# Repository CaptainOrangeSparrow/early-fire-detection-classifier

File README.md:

# Early-fire-detection-classifier

## Description

This repository aims to detect fires at an early stage and classify the type of fire using sensor-fusion techniques and machine learning. The project is from the University of Texas at Austin's engineering senior design group Spring 2026.

## Things that are Good to Know

### GIT

Git on the jetson is setup using the SSH key route. Any git actions will not prompt a log in due to the stored SSH deploy key. Pushes will be recorded as have been made by the deploy key. Whoever is registered on the jetson's git config global user.email will show up as the user responsible of a commit at the time of commit.

To change the git config global user:

```git config --global user.email [git email here]```

When you want to do a COMMIT, change the git config global user email to your git email or sign your first name at the end of your commit message (For example add file -firstname).

Once you attempt to PUSH your changes, you will then be prompted with the following message to provide a passphrase for security (this passphrase is shared among the team members):

```Enter passphrase for key '/home/firedistinguisher/.ssh/id_ed25519':```

AFTER you finish pushing your changes and making edits, consider running the following command to clear the user.email environment variable so the next developer will be automatically reminded to provide their email when making their commits, thanks!

```git config --global --unset user.email```

-----

### SSH

To log onto the jetson from the ECE-LRC servers:

```ssh firedistinguisher@localhost -p 2000```

To log onto the jetson from the ECE-LRC servers with video forwarding:

```ssh firedistinguisher@localhost -p 2000 -Y```

To log onto the jetson from your laptop through the ECE-LRC servers to support web-streaming from local host on the jeston to your local browser:

```ssh ssh -J eid@mario.ece.utexas.edu -p 2000 firedistinguisher@localhost -L [port]:localhost:[port]```

- Replace [port] with the port number the web stream is hosted on or streaming to

-----

### CONDA Virtual Environment Manager

Available CONDA environments:

- base
- app
- appgui
- cameragui
- recording
- telemetry

Please do not modify the base environment.

-----

## Repository Structure

**I2C-testing**

This folder contains code to test accessing read-write functionality on the I2C bus using python smbus2 module for various connected devices including the ADC and HDC. Use i2cdetect -r to scan I2C busses for connected devices.

- ```basic-I2C.py``` sends read and write commands on the i2c bus
- ```ads1115-i2c.py``` is a class that reads values from the ads1115 modules
- ```hdc3022.py``` is a class that reads values from the hdc3022 temp and humidity sensor

Requires ```recording``` conda env.

-----

**audio-testing**

This folder contains code for testing the MAX98357A Audio Amp for producing audio from the jetson using the I2S protocol. 

- ```play-tone.py``` plays a sine wave for a specified duration and frequency
- ```play-wav.py``` plays a wav file

Requires ```recording``` conda env.

-----

**camera-gui**

This folder contains original python gui that was developed to play prerecorded mp4 files. A pyside 6 gui application is used to display the videos and interactive buttons.

- ```camera_gui.ipynb``` is the original python notebook that was used to develop the initial gui
- ```camera_gui.py``` is the python version of the ipynb notebook  
- ```test.txt``` is a test file

Requires ```cameragui``` conda env.

-----

**camera-testing**

This folder contains tools to view the raw camera streams for RGB and IR cameras. In particular, it contains code for the tc001. The raw camera streams open native openCV windows or host a web stream. NOTE: The tc001 code came from another repo leswright pythermalcam and contains some erroneous temperature decoding code. (That is fixed in the data recording camera module)

- ```readme```: This folder comes with its own readme. See readme for more details
- ```web-stream-camera.py``` is the web stream version of stream-camera.py. Note: to use the web-stream, the ssh port forwarding needs to be used. (See web stream ssh command above).

Requires ```cameragui``` conda env.

-----

**data-recording**

This is the main data recording software folder. Multi-modal data is recorded and streamed using either a pyside6 gui application, console only mode, or web stream application (recommended). Data is recorded at a default 25 FPS.

Recordings are saved to saved_recordings [dir] and test_recordings [dir] hold recordings that were taken just for testing and are kept for historical purposes.

- ```readme.txt```: This folder comes with its own readme. See readme for more details
- ```record.py``` is the main data recording script```
- ```utilities``` [dir] holds utility modules such as writers, web stream host server, html, javascript, etc. and other helpful utility code
- ```peripherals``` [dir] holds modules containing classes to read info and interact with connected external devices such as cameras and adcs.
- ```saved_recordings``` [dir] holds saved recordings
- ```test_recordings``` [dir] holds test recordings
- ```clear_Saved_to_test.py``` is a helper script to move all recordings in saved_recordings to test_recordings
- ```gstreamer_test.py``` is a helper script to test using gstreamer to run nvidia hardware optimized camera frames
- ```verify-frame-count.py``` is a helper script to count the number of frames in every mp4 file in a specified directory (does not search child directories)

Requires ```recording``` conda env.

-----

**downloads**

The purpose of this folder is to store files in transit (Files that needed to be copied over into or exported out of the jeston).

-----

**stream-camera-gui**

This folder contains files to stream both RGB and IR camera feeds simultaneously with a more custom gui in a pyside6 application

- ```readme.txt```: This folder comes with its own readme. See readme for more details. This readme has details for the rest of the components in the folder and therefore the other contents in the folder won't be listed again here.

Requires ```appgui``` conda env.

-----

**telemetry-display**

This folder contains files to stream data to a ST7735 LCD display.

Requires ```telemetry``` conda env.

-----

**test-files**

This folder contains miscellaneous test files.

----

## Additional Notes

Thanks, add anything other considerations here if need be.

Michael

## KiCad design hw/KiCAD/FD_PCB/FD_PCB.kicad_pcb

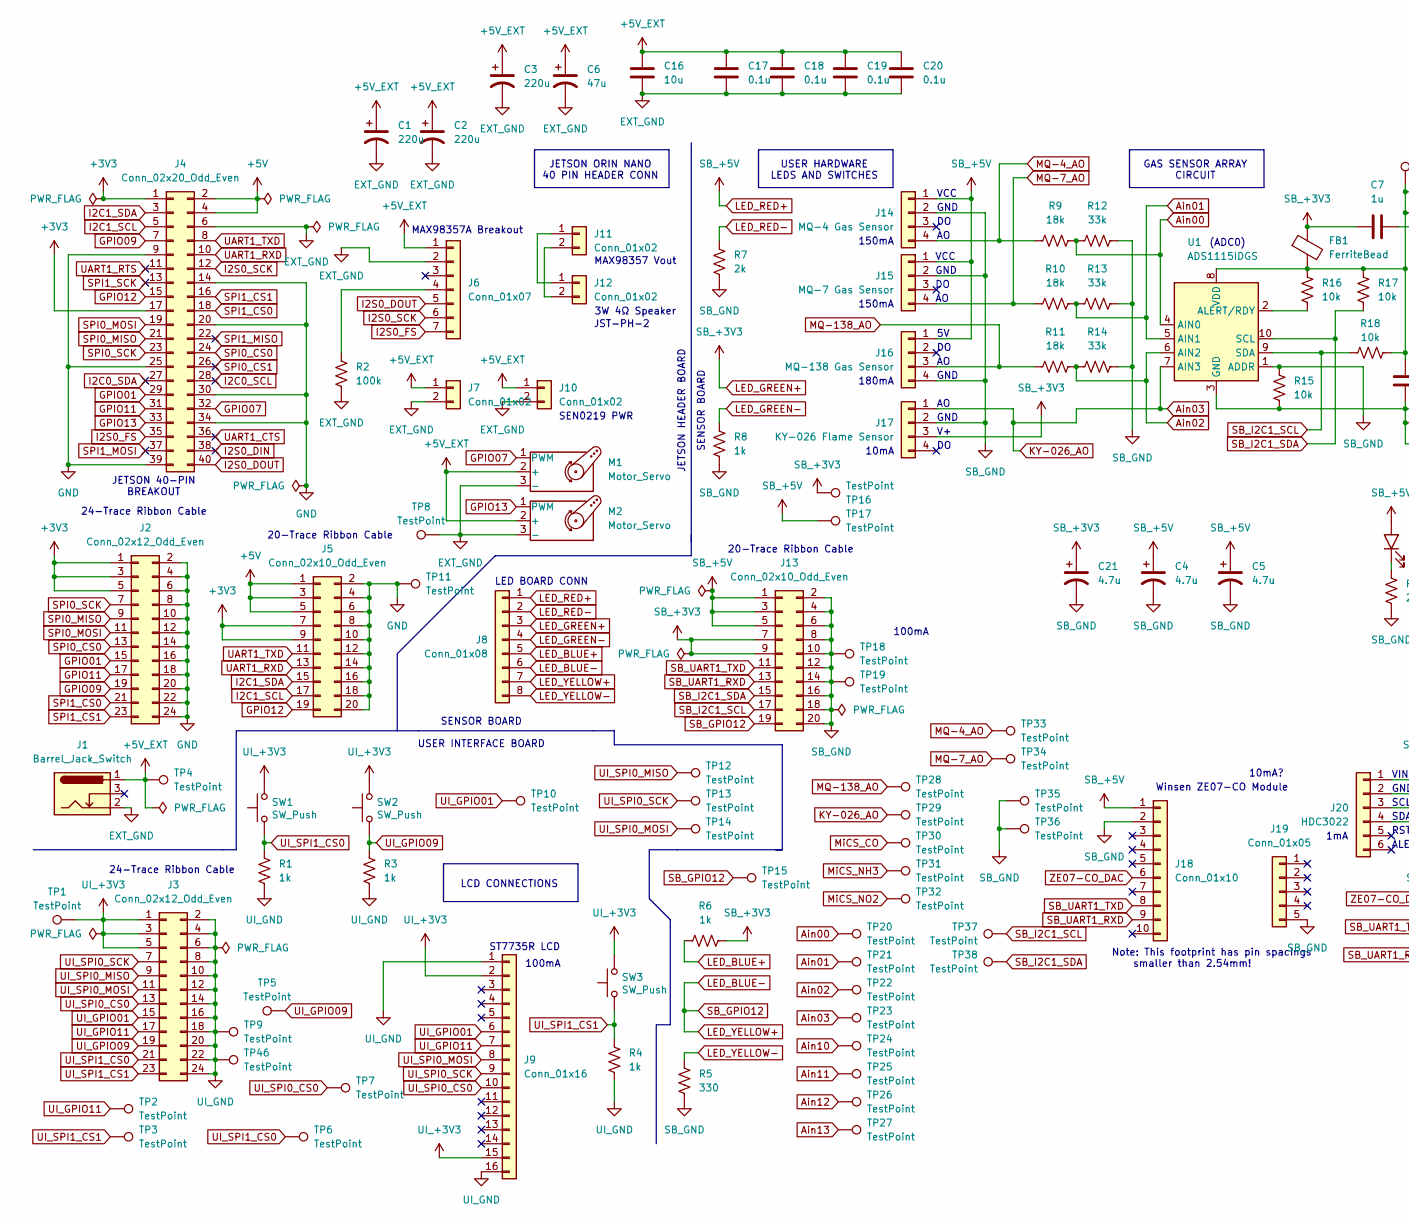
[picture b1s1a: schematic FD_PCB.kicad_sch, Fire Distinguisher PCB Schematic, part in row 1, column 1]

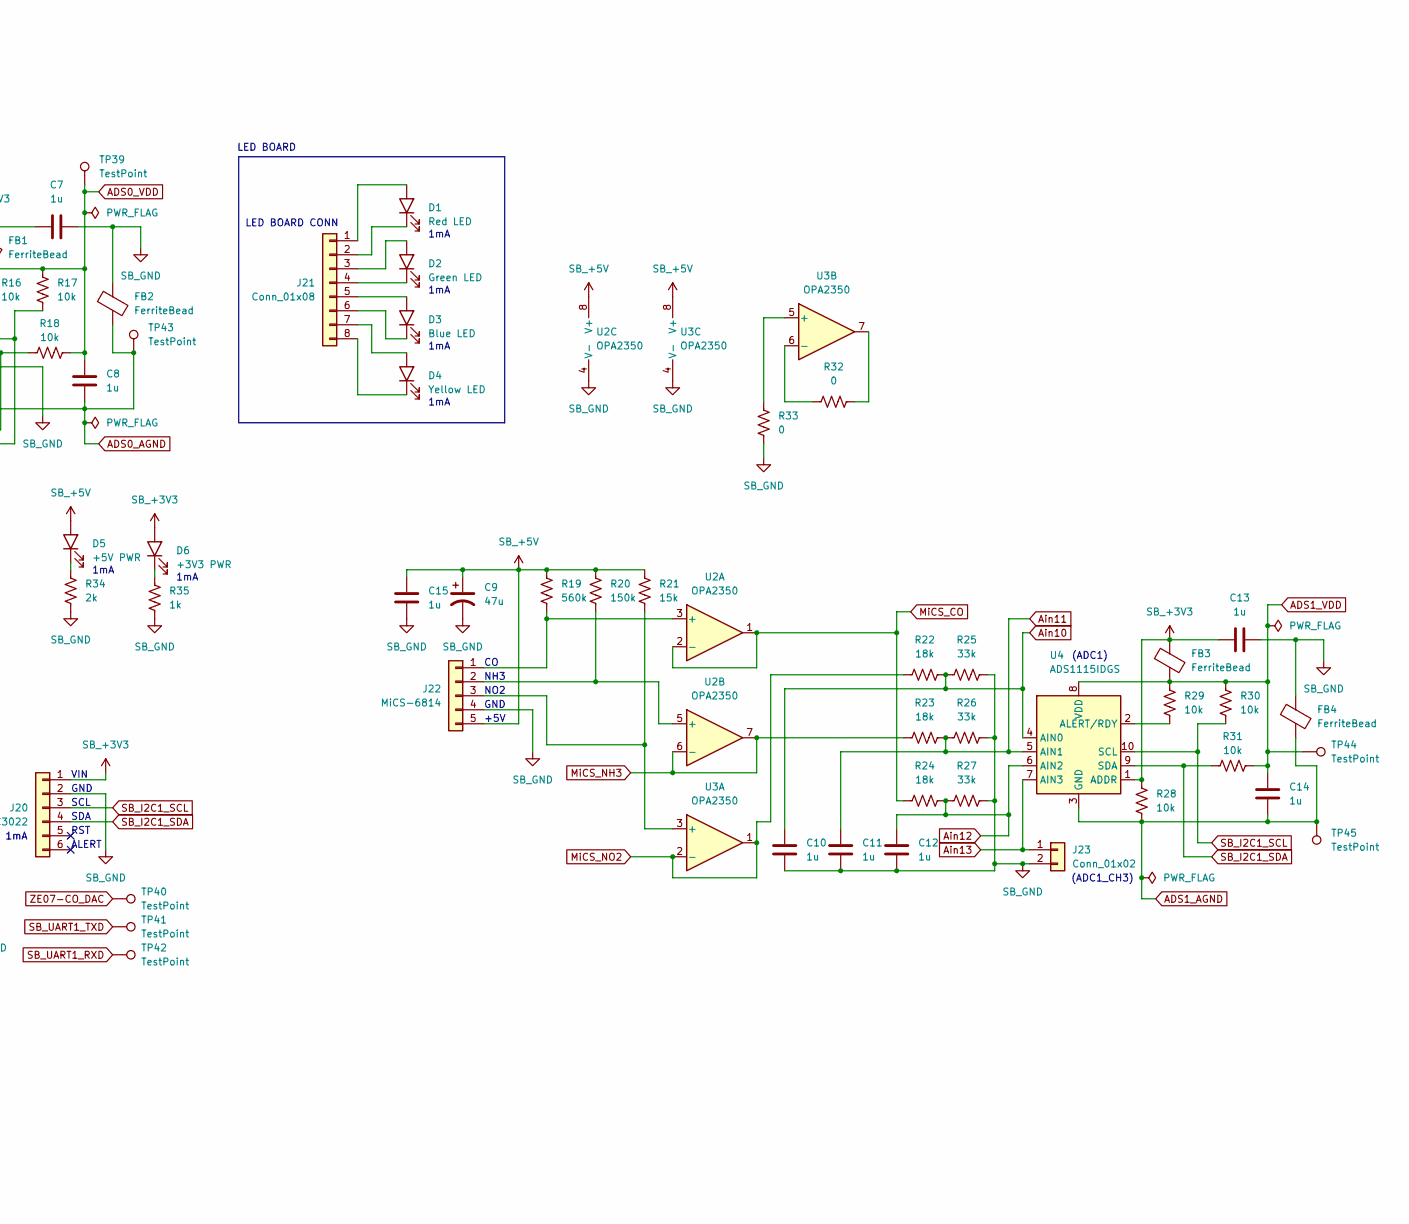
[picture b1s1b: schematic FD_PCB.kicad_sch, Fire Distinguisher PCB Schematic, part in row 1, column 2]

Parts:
C1, C2, C3: 220u; CP_Radial_Tantal200mil
C4, C5, C21: 4.7u; CP_Radial_Tantal200mil
C6, C9: 47u; CP_Radial_Tantal200mil
C7, C8, C10, C11, C12, C13, C14, C15: 1u; C_0805_2012Metric
C16: 10u; C_Axial_200mil
C17, C18, C19, C20: 0.1u; C_0805_2012Metric
D1: Red LED; LED_D5.0mm
D2: Green LED; LED_D5.0mm
D3: Blue LED; LED_D5.0mm
D4: Yellow LED; LED_D5.0mm
D5: +5V PWR; LED_D5.0mm
D6: +3V3 PWR; LED_D5.0mm
FB1, FB2, FB3, FB4: FerriteBead; R_0603_1608Metric
J1: Barrel_Jack_Switch; BarrelJack_Wuerth_6941xx301002
J2, J3: Conn_02x12_Odd_Even; PinHeader_2x12_P2.54mm_Vertical
J4: Conn_02x20_Odd_Even; PinHeader_2x20_P2.54mm_Vertical
J5, J13: Conn_02x10_Odd_Even; PinHeader_2x10_P2.54mm_Vertical
J6: Conn_01x07; PinHeader_1x07_P2.54mm_Vertical
J7, J10, J11, J23: Conn_01x02; PinHeader_1x02_P2.54mm_Vertical
J8, J21: Conn_01x08; PinHeader_1x08_P2.54mm_Vertical
J9: Conn_01x16; PinHeader_1x16_P2.54mm_Vertical
J12: Conn_01x02; JST_PH_B2B-PH-K_1x02_P2.00mm_Vertical
J14: MQ-4 Gas Sensor; PinHeader_1x04_P2.54mm_Vertical
J15: MQ-7 Gas Sensor; PinHeader_1x04_P2.54mm_Vertical
J16: MQ-138 Gas Sensor; PinHeader_1x04_P2.54mm_Vertical
J17: KY-026 Flame Sensor; PinHeader_1x04_P2.54mm_Vertical
J18: Conn_01x10; PinHeader_1x10_P2.00mm_Vertical
J19: Conn_01x05; PinHeader_1x05_P2.00mm_Vertical
J20: HDC3022; PinHeader_1x06_P2.54mm_Vertical
J22: MiCS-6814; PinHeader_1x05_P2.54mm_Vertical
M1, M2: Motor_Servo; PinHeader_1x03_P2.54mm_Vertical
R1, R3, R4, R6, R8, R35: 1k; R_0805_2012Metric
R2: 100k; R_0805_2012Metric
R5: 330; R_0805_2012Metric
R7, R34: 2k; R_0805_2012Metric
R9, R10, R11, R22, R23, R24: 18k; R_0805_2012Metric
R12, R13, R14, R25, R26, R27: 33k; R_0805_2012Metric
R15, R16, R17, R18, R28, R29, R30, R31: 10k; R_0805_2012Metric
R19: 560k; R_0805_2012Metric
R20: 150k; R_0805_2012Metric
R21: 15k; R_0805_2012Metric
R32, R33: 0; R_0805_2012Metric
SW1, SW2, SW3: SW_Push; SW_PUSH_6mm
TP1, TP2, TP3, TP4, TP5, TP6, TP7, TP8, TP9, TP10, TP11, TP12, TP13, TP14, TP15, TP16, TP17, TP18, TP19, TP20, TP21, TP22, TP23, TP24, TP25, TP26, TP27, TP28, TP29, TP30, TP31, TP32, TP33, TP34, TP35, TP36, TP37, TP38, TP39, TP40, TP41, TP42, TP43, TP44, TP45, TP46: TestPoint; TestPoint_Loop_D3.50mm_Drill1.4mm_Beaded
U1, U4: ADS1115IDGS; TSSOP-10_3x3mm_P0.5mm
U2, U3: OPA2350; DIP-8_W7.62mm_LongPads

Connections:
+3V3: J2.1, J2.3, J2.5, J4.1, J4.17, J5.7, J5.9
+5V: J4.2, J4.4, J5.1, J5.3, J5.5
+5V_EXT: C1.1, C2.1, C3.1, C6.1, C16.1, C17.1, C18.1, C19.1, C20.1, J1.1, J6.1, J7.1, J10.1, M1.2 (+), M2.2 (+), TP4.1
ADS0_AGND: C8.2, FB2.2, R15.2, TP43.1, U1.3 (GND)
ADS0_VDD: C8.1, FB1.2, R16.1, R17.1, R18.2, TP39.1, U1.8 (VDD)
ADS1_AGND: C14.2, FB4.2, R28.2, TP45.1, U4.3 (GND)
ADS1_VDD: C14.1, FB3.2, R29.1, R30.1, R31.2, TP44.1, U4.8 (VDD)
Ain00: R9.1, R12.1, TP20.1, U1.4 (AIN0)
Ain01: R10.1, R13.1, TP21.1, U1.5 (AIN1)
Ain02: R11.1, R14.1, TP22.1, U1.6 (AIN2)
Ain03: J17.1, TP23.1, TP29.1, U1.7 (AIN3)
Ain10: C10.1, R22.1, R25.1, TP24.1, U4.4 (AIN0)
Ain11: C11.1, R23.1, R26.1, TP25.1, U4.5 (AIN1)
Ain12: C12.1, R24.1, R27.1, TP26.1, U4.6 (AIN2)
Ain13: J23.1, TP27.1, U4.7 (AIN3)
EXT_GND: C1.2, C2.2, C3.2, C6.2, C16.2, C17.2, C18.2, C19.2, C20.2, J1.2, J4.6, J6.2, J7.2, J10.2, M1.3 (-), M2.3 (-), R2.1, TP8.1
GND: J2.2, J2.4, J2.6, J2.8, J2.10, J2.12, J2.14, J2.16, J2.18, J2.20, J2.22, J2.24, J4.9, J4.14, J4.20, J4.25, J4.30, J4.34, J4.39, J5.2, J5.4, J5.6, J5.8, J5.10, J5.12, J5.14, J5.16, J5.18, J5.20, TP11.1
GPIO01: J2.15, J4.29
GPIO07: J4.32, M1.1 (PWM)
GPIO09: J2.19, J4.7
GPIO11: J2.17, J4.31
GPIO12: J4.15, J5.19
GPIO13: J4.33, M2.1 (PWM)
I2C0_SCL: J4.28
I2C0_SDA: J4.27
I2C1_SCL: J4.5, J5.17
I2C1_SDA: J4.3, J5.15
I2S0_DIN: J4.38
I2S0_DOUT: J4.40, J6.5
I2S0_FS: J4.35, J6.7
I2S0_SCK: J4.12, J6.6
LED_BLUE+: J8.5, R6.2
LED_BLUE-: J8.6, J8.7, J13.19, TP15.1
LED_GREEN+: C7.1, C13.1, C21.1, D6.2 (A), FB1.1, FB3.1, J8.3, J13.7, J13.9, J17.3, J20.1, R6.1, R28.1, TP16.1, U4.1 (ADDR)
LED_GREEN-: J8.4, R8.2
LED_RED+: C4.1, C5.1, C9.1, C15.2, D5.2 (A), J8.1, J13.1, J13.3, J13.5, J14.1, J15.1, J16.1, J18.1, J22.5, R19.1, R20.1, R21.1, TP17.1, U2.8 (V+), U3.8 (V+)
LED_RED-: J8.2, R7.2
LED_YELLOW-: J8.8, R5.2
MQ-4_AO: J14.4, R9.2, TP33.1
MQ-7_AO: J15.4, R10.2, TP34.1
MQ-138_AO: J16.3, R11.2, TP28.1
MiCS_CO: R24.2, TP30.1, U2.1, U2.2 (-)
MiCS_NH3: R23.2, TP31.1, U2.6 (-), U2.7
MiCS_NO2: R22.2, TP32.1, U3.1, U3.2 (-)
unnamed: D1.2 (A), J21.1
unnamed: D1.1 (K), J21.2
unnamed: D2.2 (A), J21.3
unnamed: D2.1 (K), J21.4
unnamed: D3.2 (A), J21.5
unnamed: D3.1 (K), J21.6
unnamed: D4.2 (A), J21.7
unnamed: D4.1 (K), J21.8
unnamed: D5.1 (K), R34.2
unnamed: D6.1 (K), R35.2
unnamed: J6.4, R2.2
unnamed: J11.1, J12.1
unnamed: J11.2, J12.2
unnamed: J22.1, R19.2, U2.3 (+)
unnamed: J22.2, R20.2, U2.5 (+)
unnamed: J22.3, R21.2, U3.3 (+)
unnamed: R32.1, U3.7
unnamed: R16.2, U1.2 (ALERT/RDY)
unnamed: R33.2, U3.5 (+)
unnamed: R32.2, U3.6 (-)
unnamed: R29.2, U4.2 (ALERT/RDY)
SB_GND: C4.2, C5.2, C7.2, C9.2, C10.2, C11.2, C12.2, C13.2, C15.1, C21.2, FB2.1, FB4.1, J13.2, J13.4, J13.6, J13.8, J13.10, J13.12, J13.14, J13.16, J13.18, J13.20, J14.2, J15.2, J16.4, J17.2, J18.2, J19.5, J20.2, J22.4, J23.2, R5.1, R7.1, R8.1, R12.2, R13.2, R14.2, R15.1, R25.2, R26.2, R27.2, R33.1, R34.1, R35.1, TP18.1, TP19.1, TP35.1, TP36.1, U1.1 (ADDR), U2.4 (V-), U3.4 (V-)
SB_I2C1_SCL: J13.17, J20.3, R18.1, R30.2, TP37.1, U1.9 (SDA), U4.10 (SCL)
SB_I2C1_SDA: J13.15, J20.4, R17.2, R31.1, TP38.1, U1.10 (SCL), U4.9 (SDA)
SB_UART1_RXD: J13.13, J18.9, TP42.1
SB_UART1_TXD: J13.11, J18.8, TP41.1
SPI0_CS0: J2.13, J4.24
SPI0_CS1: J4.26
SPI0_MISO: J2.9, J4.21
SPI0_MOSI: J2.11, J4.19
SPI0_SCK: J2.7, J4.23
SPI1_CS0: J2.21, J4.18
SPI1_CS1: J2.23, J4.16
SPI1_MISO: J4.22
SPI1_MOSI: J4.37
SPI1_SCK: J4.13
UART1_CTS: J4.36
UART1_RTS: J4.11
UART1_RXD: J4.10, J5.13
UART1_TXD: J4.8, J5.11
UI_+3V3: J3.1, J3.3, J3.5, J9.2, J9.15, SW1.2, SW2.2, SW3.2, TP1.1
UI_GND: J3.2, J3.4, J3.6, J3.8, J3.10, J3.12, J3.14, J3.16, J3.18, J3.20, J3.22, J3.24, J9.1, J9.16, R1.1, R3.1, R4.1, TP9.1, TP46.1
UI_GPIO01: J3.15, J9.6, TP10.1
UI_GPIO09: J3.19, R3.2, SW2.1, TP5.1
UI_GPIO11: J3.17, J9.7, TP2.1
UI_SPI0_CS0: J3.13, J9.10, TP7.1
UI_SPI0_MISO: J3.9, TP12.1
UI_SPI0_MOSI: J3.11, J9.8, TP14.1
UI_SPI0_SCK: J3.7, J9.9, TP13.1
UI_SPI1_CS0: J3.21, R1.2, SW1.1, TP6.1
UI_SPI1_CS1: J3.23, R4.2, SW3.1, TP3.1
ZE07-CO_DAC: J18.6, TP40.1

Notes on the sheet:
1mA
24-Trace Ribbon Cable
3W 4Ω Speaker
NH3
VCC
10mA?
20-Trace Ribbon Cable
GND
JETSON HEADER BOARD
MAX98357 Vout
JETSON ORIN NANO 40 PIN HEADER CONN
SCL
VIN
SDA
Winsen ZE07-CO Module
MAX98357A Breakout
(ADC1_CH3)
(ADC0)
JST-PH-2
GAS SENSOR ARRAY CIRCUIT
USER HARDWARE LEDS AND SWITCHES
ST7735R LCD
150mA
SENSOR BOARD
100mA
LED BOARD CONN
ALERT
10mA
180mA
JETSON 40-PIN BREAKOUT
(ADC1)
Note: This footprint has pin spacings smaller than 2.54mm!
LCD CONNECTIONS
LED BOARD
NO2
RST
USER INTERFACE BOARD
+5V
SEN0219 PWR

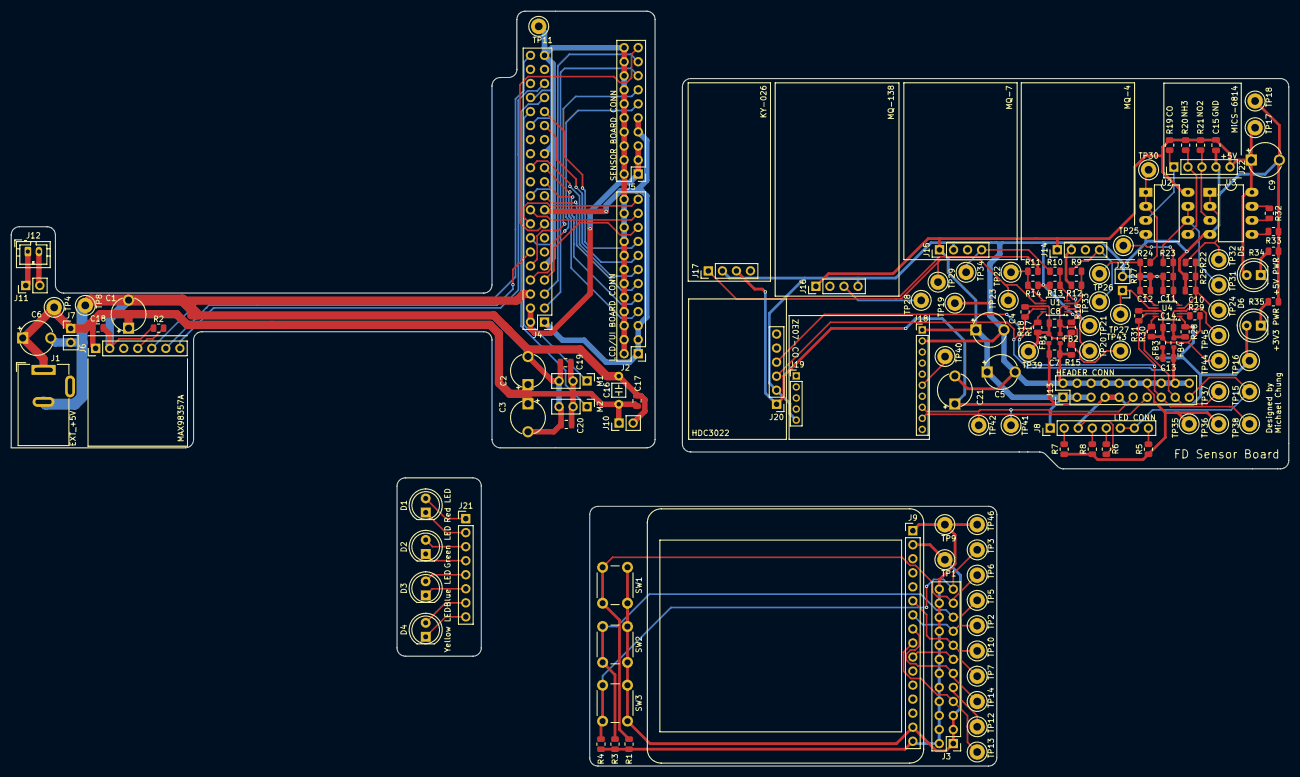
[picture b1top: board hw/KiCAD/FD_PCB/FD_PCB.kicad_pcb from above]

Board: 2 copper layers, 231.2 x 136.6 mm, 144 parts (0 on the bottom side), 87 nets.

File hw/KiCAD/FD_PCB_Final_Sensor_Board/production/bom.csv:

Designator,Footprint,Quantity,Value,LCSC Part #
"C10, C11, C12, C13, C14, C15, C7, C8",0805,8,1u,
"C21, C4, C5",CP_Radial_Tantal200mil,3,4.7u,
C9,CP_Radial_Tantal200mil,1,47u,
D5,LED_D5.0mm,1,+5V PWR,
D6,LED_D5.0mm,1,+3V3 PWR,
"FB1, FB2, FB3, FB4",0603,4,FerriteBead,
"H11, H12, H13, H14, H15, H16",MountingHole_4_40,6,~,
J13,PinHeader_2x10_P2.54mm_Vertical,1,Conn_02x10_Odd_Even,
J14,PinHeader_1x04_P2.54mm_Vertical,1,MQ-4 Gas Sensor,
J15,PinHeader_1x04_P2.54mm_Vertical,1,MQ-7 Gas Sensor,
J16,PinHeader_1x04_P2.54mm_Vertical,1,MQ-138 Gas Sensor,
J17,PinHeader_1x04_P2.54mm_Vertical,1,KY-026 Flame Sensor,
J18,PinHeader_1x10_P2.00mm_Vertical,1,Conn_01x10,
J19,PinHeader_1x05_P2.00mm_Vertical,1,Conn_01x05,
J20,PinHeader_1x06_P2.54mm_Vertical,1,HDC3022,
J22,PinHeader_1x05_P2.54mm_Vertical,1,MiCS-6814,
J23,PinHeader_1x02_P2.54mm_Vertical,1,Conn_01x02,
J8,PinHeader_1x08_P2.54mm_Vertical,1,Conn_01x08,
"R10, R11, R22, R23, R24, R9",0805,6,18k,
"R12, R13, R14, R25, R26, R27",0805,6,33k,
"R15, R16, R17, R18, R28, R29, R30, R31",0805,8,10k,
R19,0805,1,560k,
R20,0805,1,150k,
R21,0805,1,15k,
"R32, R33",0805,2,0,
"R34, R7",0805,2,2k,
"R35, R6, R8",0805,3,1k,
R5,0805,1,330,
"TP15, TP16, TP17, TP18, TP19, TP20, TP21, TP22, TP23, TP24, TP25, TP26, TP27, TP28, TP29, TP30, TP31, TP32, TP33, TP34, TP35, TP36, TP37, TP38, TP39, TP40, TP41, TP42, TP43, TP44, TP45",TestPoint_Loop_D3.50mm_Drill1.4mm_Beaded,31,TestPoint,
"U1, U4",TSSOP-10_3x3mm_P0.5mm,2,ADS1115IDGS,
"U2, U3",DIP-8_W7.62mm_LongPads,2,OPA2350,

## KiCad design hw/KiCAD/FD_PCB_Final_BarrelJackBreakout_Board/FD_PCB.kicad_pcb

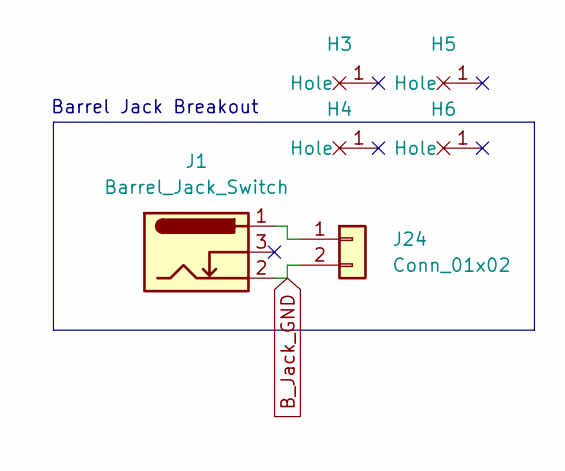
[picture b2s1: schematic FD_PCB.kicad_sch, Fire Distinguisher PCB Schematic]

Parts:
H3, H4, H5, H6: MountingHole_4_40
J1: Barrel_Jack_Switch; BarrelJack_Wuerth_6941xx301002
J24: Conn_01x02; PinHeader_1x02_P2.54mm_Vertical

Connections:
B_Jack_GND: J1.2, J24.2
unnamed: J1.1, J24.1

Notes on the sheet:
Barrel Jack Breakout

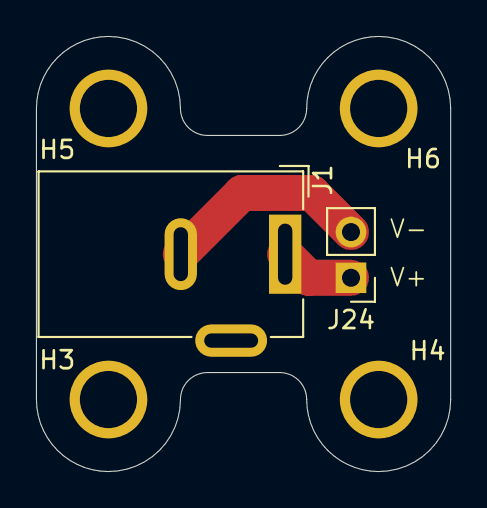
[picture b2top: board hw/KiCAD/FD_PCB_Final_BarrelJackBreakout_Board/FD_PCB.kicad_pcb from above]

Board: 2 copper layers, 23.0 x 24.2 mm, 6 parts (0 on the bottom side), 2 nets.

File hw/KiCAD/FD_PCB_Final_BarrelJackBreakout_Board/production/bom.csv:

Designator,Footprint,Quantity,Value,LCSC Part #
"H3, H4, H5, H6",MountingHole_4_40,4,~,
J1,BarrelJack_Wuerth_6941xx301002,1,Barrel_Jack_Switch,
J24,PinHeader_1x02_P2.54mm_Vertical,1,Conn_01x02,

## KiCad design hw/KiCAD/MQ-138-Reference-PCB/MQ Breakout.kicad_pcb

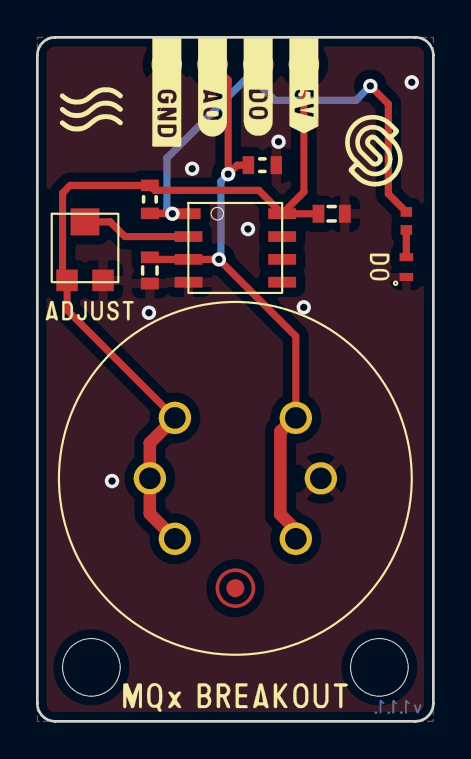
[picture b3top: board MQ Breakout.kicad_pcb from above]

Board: 2 copper layers, 22.0 x 38.0 mm, 13 parts (1 on the bottom side), 6 nets.

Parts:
C1, C2: 0.1uF; 0603C
D1: purple; 0402LED
FD1: FIDUCIAL; FIDUCIAL_23
H1, H2: HOLE_3.2mm
K1: HEADER_MALE_4X1
R1, R3: 10k; 0603R
R2: TC33X-2-103E; tc33x-2-103e
R4: 2k2; 0402R
U1: MQ-X; MQ
U2: LM393; SOIC−8

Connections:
5V: C2.2, K1.4, R2.1, R3.2, U1.1 (A), U1.2 (H), U1.3 (A), U2.8 (VCC)
AO: C1.2, K1.2, R1.2, U1.4 (B), U1.6 (B), U2.3 (1_IN+)
D0: K1.3, R3.1, R4.1, U2.1 (1_OUT)
GND: C1.1, C2.1, D1.2 (K), K1.1, R1.1, R2.3, U1.5 (H), U2.4 (GND)
unnamed: D1.1 (A), R4.2
POT: R2.2, U2.2 (1_IN-)

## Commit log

2026-01-29 add txt file test commit from jetson nano
2026-01-29 edit hi from jetson test file
2026-01-29 test 2am again
2026-01-29 move all current jetson project files to repo
2026-01-29 add downloads file transfer folder
2026-01-29 Updated main readme.md
2026-01-30 Successful Test of PWM Servo Control on Pin 33
2026-01-30 MC test after setting up orin nano ssh key
2026-01-30 MC testing orin ssh key setup again
2026-01-30 Update README.md -Moby
2026-02-02 Untested Servo Mount Class Files
2026-02-02 Untested Servo Mount Control Class
2026-02-04 Update CameraMount2Axis.py
    Bug Fix: Changed Servo to servo.Servo
2026-02-04 Update servo.py
    Feature Addition: Added Several Transition Types to Test
2026-02-04 Update CameraMount2Axis.py
    Bug Fix: Made transition type and transition speed available to CameraMount2Axis class
2026-02-04 Added a command-line test script for the servos
2026-02-04 Added README for servo test file
2026-02-08 update data recording script
2026-02-08 add hdc3022.py
2026-02-08 interface audio
2026-02-08 add gpio testing scripts
2026-02-08 add uart testing scripts
2026-02-08 Bug Fix: Calibrated Servo Control
    -Both Pan and Tilt Servos now have a range of motion of 0-180 degrees
    -Tilt Servo: 0 degrees - UP, 90 degrees - Straight, 180 degrees - Down
    -Pan Servo: 90 degrees - Center
2026-02-09 Feature: Added new transition type tests
2026-02-09 Feature: Added Command Line Camera Controller
2026-02-09 fix chartjs issue in data recording script
2026-02-09 modify gpio testing scripts
2026-02-09 Fix: Update Servo Control
2026-02-09 AJ: update to do list for servos
2026-02-11 rename uart folder and update uart testing scripts
2026-02-11 remove old uart testing folder name
2026-02-21 Add ZE07 sensor class, succesfully interfaced SEN0219 and ZE07-CO sensors to data collection script
2026-02-21 add ZE07 testing module for uart testing with 40-pin header uart pins
2026-02-22 change axis colors for temp humidity
2026-02-23 AJ: Updated gitignore file to exclude recordings
2026-02-23 AJ: Fixed Jitter Issue and added Clamping on Servos
2026-02-24 fix gpio yayayayayayay finally wow why was this so hard oh and tested gpio stuff too
2026-02-24 modify data recording script
2026-03-04 add gpio read test script
2026-03-04 fix IR writer latency issue. Added dedicated thread + double buffering
2026-03-04 fix IR writer latency issue. Switched to uncompressed npz. Added test files. Edit: Keeping test files untracked due to large size
2026-03-04 exited vim and remove swp file
2026-03-04 implement gstreamer
2026-03-05 update buffered ir writer
2026-03-06 AJ: Pushing Changes to telemetry-display
2026-03-07 AJ: Implemented FSM to Control Telemetry Display Live View
2026-03-07 AJ: Successfull multiview detection
2026-03-07 AJ: Color conversion bug MultiViewDisplay.py
2026-03-07 fix view only run dir
2026-03-07 modify gitignore
2026-03-09 AJ: implemented async method to control display
2026-03-09 AJ: Successful implementation of Telemetry Display with threading
2026-03-23 create final gui and start combining projects
2026-03-23 close webstream on program end
2026-03-23 modify git ignore
2026-03-23 upload KiCAD projects
2026-03-24 Created ML modules and fixed warnings in the printing outputs. Updated testing real-time for testing live data streams. -Moby
2026-03-24 complete ML integration and add audio integration
2026-03-24 add data recording run script
2026-03-24 convert sounds
2026-03-24 updated venv stuff
2026-03-24 update kicad stuff
2026-03-26 add global audio player
2026-03-29 AJ: Fixing Merge Conflict
2026-03-29 Update gitignore
2026-03-29 AJ: Implement Multi-threading to Camera Mount in Prep. for PID implementation
2026-03-30 AJ: First implementation of PID controller without tuning
2026-03-31 AJ: Successful P-controller Track Implementation
2026-03-31 AJ: Added PSD Analysis for Gas Sensors
2026-04-02 Finish schematic and start on PCB design. Much progress.
2026-04-04 finish sensor board, lcd board, led board, and header board
2026-04-05 finish adding mouting holes and do some prints
2026-04-05 add silkscreen, generate latest print p3-104
2026-04-05 rename with peninsula
2026-04-05 update gui and ir camera api for temp frames
2026-04-05 update ml for live fire detection
2026-04-06 fix header board collision dimensions, add additional mounting hole on header board
2026-04-06 add measurement for H20
2026-04-06 update mounting hole position for H17 and H18
2026-04-06 Decorate Silkscreen
2026-04-06 generate prints
2026-04-06 finalize pcb
2026-04-06 separate boards and generate pcb production gerber files
2026-04-06 AJ: update repo after data recording session
2026-04-06 AJ: fixing merge conflit
2026-04-06 AJ: Preparing for demo
2026-04-07 fix IR frame issue
2026-04-07 fix typos, fix IR camera frame issue
2026-04-13 AJ: Update Repo
2026-04-13 Add fd_main_v3 containing refactored fire_tracker class
    Removed the tracking logic from fd_main and placed PID and ObjCenter classes into a comprehensive fire_tracker class. This class builds the servo mount class, PID control loops for each servo, and ha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
2026-04-13 Upload Refactored Version of Pan-Tilt Tracker Unified into a single file
2026-04-13 AJ: Fix fd_main_v3 pwm frequency
2026-04-14 AJ: Stablized PI Controller By Adding a Deadzone
2026-04-15 Pushing updates for AJ. -Moby
2026-04-19 save copies of device tree overlays
2026-04-19 enable spi3 pins
2026-04-19 fix fs cs gpio pinmux assignments
2026-04-19 fix cts pinmux pin name
2026-04-19 try servo controls, add SPI DAC
2026-04-27 AJ: further refinement of controller
